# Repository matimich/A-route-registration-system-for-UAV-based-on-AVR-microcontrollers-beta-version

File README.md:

Author: Mateusz Michalski

Description:
A route registration system for UAV, based on AVR microcontrollers is a platform consisting of three ATmega microcontrollers, GPS module and an MicroSD card drive. One of the aims of the project was to learn as much communication interfaces as possible, that is why the project includes UART, I2C, SPI, CAN interfaces. All code has been written in C language. To communicate with MicroSD card drive "FatFs" library has been used. In addition, to make communication with CAN, MCP2515 module and MCP2551 transciver have been used. Working with this components reqiured to attached additional elements from "" library into the project.
Because project was made mostly for a educational purposes, apart from 

The project was made as diploma thesis.

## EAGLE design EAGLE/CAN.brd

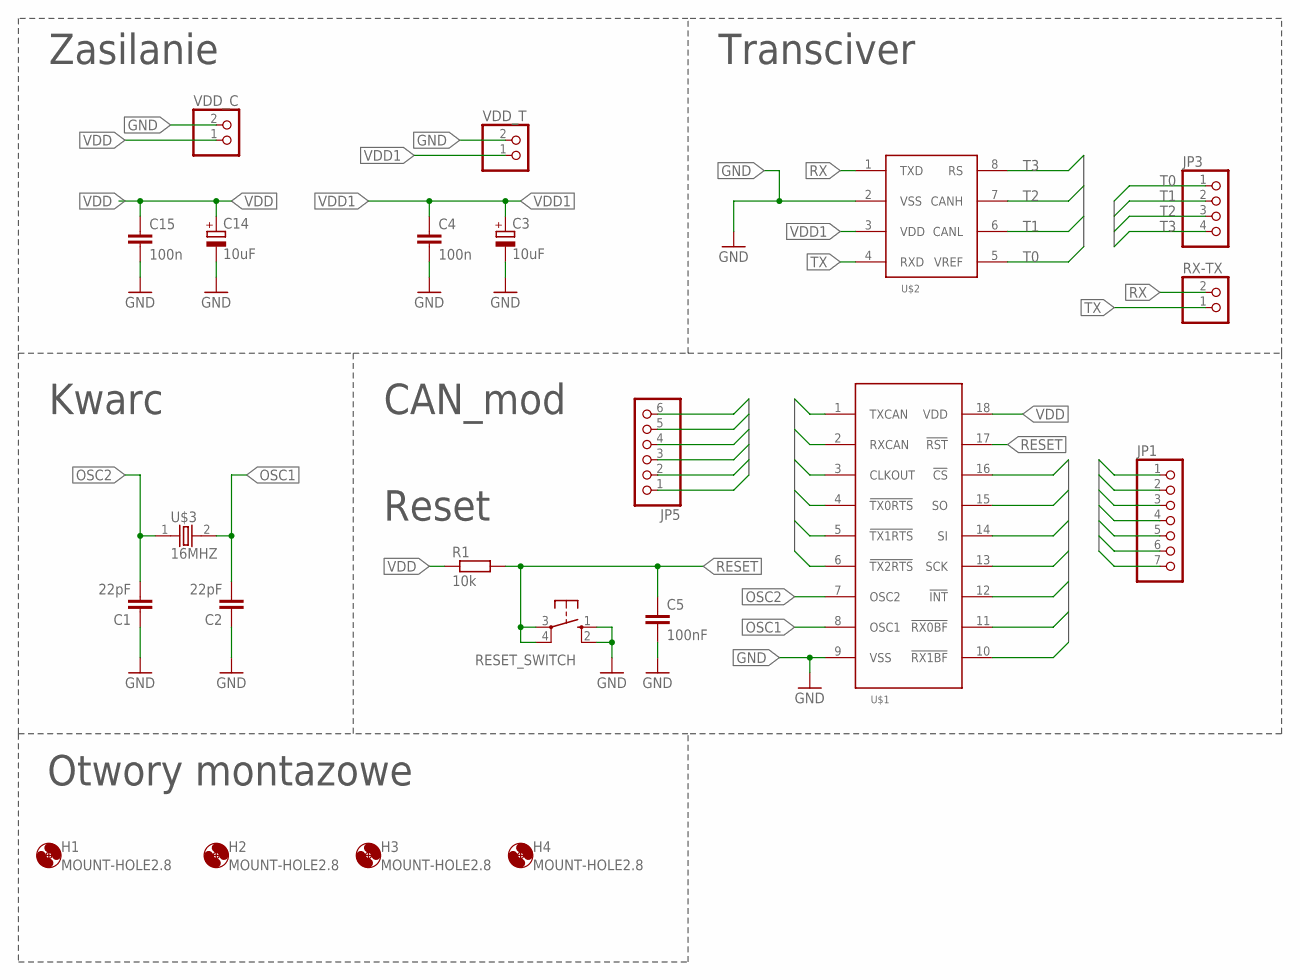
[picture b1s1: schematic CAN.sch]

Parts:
C1, C2: 22pF; C3216
C3, C14: 10uF; A/3216-18W
C4, C15: 100n; C1206K
C5: 100nF; C1206K
H1, H2, H3, H4: MOUNT-HOLE2.8; 2,8
JP1: PINHD-1X7MAT_LCD; 1X07
JP3: PINHD-1X4; 1X04
JP5: PINHD-1X6MAT6; 1X06
R1: 10k; R3216
RESET_SWITCH: 10-XX; B3F-10XX
RX-TX: PINHD-1X2; 1X02
U$1: MCP2515
U$2: MCP2551
U$3: 16MHZ; HC49SM
VDD_C: PINHD-1X2; 1X02
VDD_T: PINHD-1X2; 1X02

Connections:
CAN0: JP1.1, U$1.10 (!RX1BF)
CAN1: JP1.2, U$1.11 (!RX0BF)
CAN2: JP1.3, U$1.12 (!INT)
CAN3: JP1.4, U$1.13 (SCK)
CAN4: JP1.5, U$1.14 (SI)
CAN5: JP1.6, U$1.15 (SO)
CAN6: JP1.7, U$1.16 (!CS)
CANL0: JP5.1, U$1.6 (!TX2RTS)
CANL1: JP5.2, U$1.5 (!TX1RTS)
CANL2: JP5.3, U$1.4 (!TX0RTS)
CANL3: JP5.4, U$1.3 (CLKOUT)
CANL4: JP5.5, U$1.2 (RXCAN)
CANL5: JP5.6, U$1.1 (TXCAN)
GND: C1.1, C2.1, C3.-, C4.2, C5.2, C14.-, C15.2, RESET_SWITCH.1 (S), RESET_SWITCH.2 (S1), U$1.9 (VSS), U$2.2 (VSS), VDD_C.2 (1), VDD_T.2 (1)
OSC1: C2.2, U$1.8 (OSC1), U$3.2
OSC2: C1.2, U$1.7 (OSC2), U$3.1
RESET: C5.1, R1.2, RESET_SWITCH.3, RESET_SWITCH.4 (P1), U$1.17 (!RST)
RX: RX-TX.2 (1), U$2.1 (TXD)
T0: JP3.1, U$2.5 (VREF)
T1: JP3.2, U$2.6 (CANL)
T2: JP3.3, U$2.7 (CANH)
T3: JP3.4, U$2.8 (RS)
TX: RX-TX.1 (2), U$2.4 (RXD)
VDD: C14.+, C15.1, R1.1, U$1.18 (VDD), VDD_C.1 (2)
VDD1: C3.+, C4.1, U$2.3 (VDD), VDD_T.1 (2)

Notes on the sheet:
Zasilanie
Transciver
Kwarc
CAN_mod
Reset
Otwory montazowe

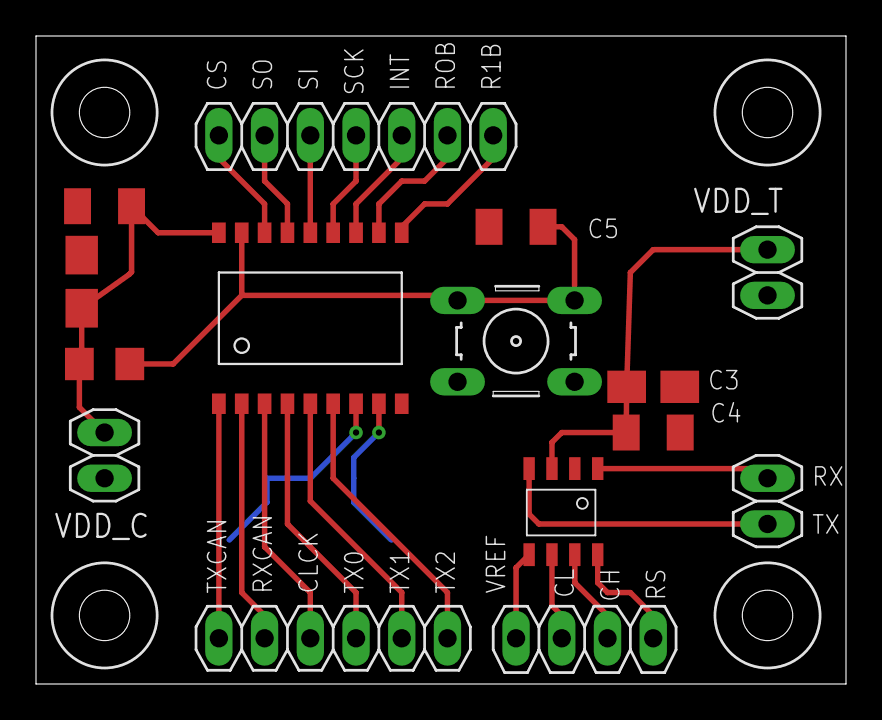
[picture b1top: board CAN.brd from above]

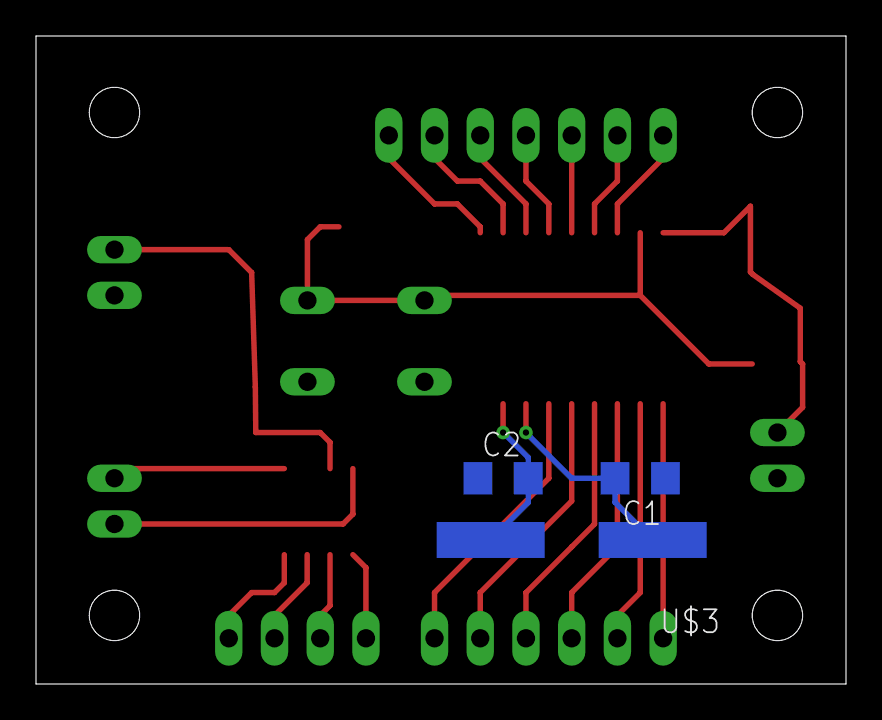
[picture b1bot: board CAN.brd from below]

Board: 2 copper layers, 45.0 x 36.0 mm, 22 parts (3 on the bottom side), 25 nets.

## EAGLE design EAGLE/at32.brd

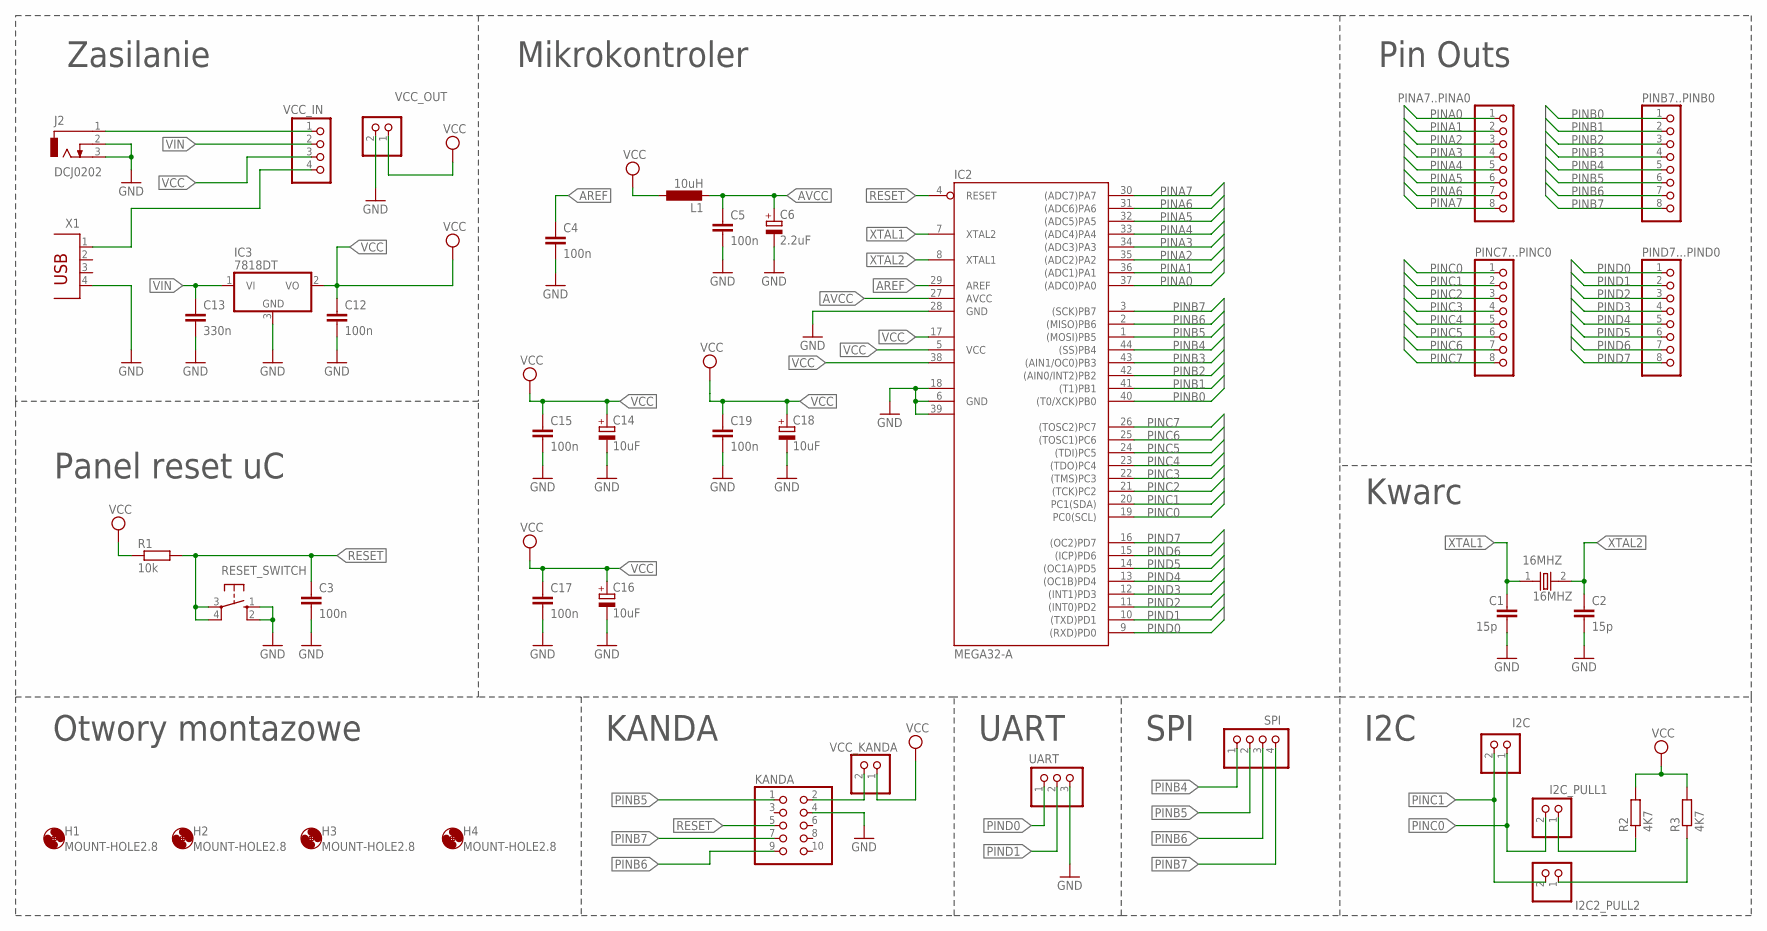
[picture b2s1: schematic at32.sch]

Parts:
16MHZ: 16MHZ; HC49SM
C1, C2: 15p; C1206K
C3, C4, C5, C12, C15, C17, C19: 100n; C1206K
C6: 2.2uF; A/3216-18W
C13: 330n; C1206K
C14, C16, C18: 10uF; A/3216-18W
H1, H2, H3, H4: MOUNT-HOLE2.8; 2,8
I2C, I2C2_PULL2, I2C_PULL1: PINHD-1X2; 1X02
IC2: MEGA32-A; TQFP44
IC3: 7818DT; TO252
J2: DCJ0202
KANDA: PINHD-2X5; 2X05
L1: 10uH; L3225M
PINA7..PINA0: PINHD-1X8MAT8; 1X08
PINB7..PINB0: PINHD-1X8MAT8; 1X08
PINC7...PINC0: PINHD-1X8MAT8; 1X08
PIND7...PIND0: PINHD-1X8MAT8; 1X08
R1: 10k; R3216
R2, R3: 4K7; R3216
RESET_SWITCH: 10-XX; B3F-10XX
SPI: PINHD-1X4; 1X04
UART: PINHD-1X3; 1X03
VCC_IN: PINHD-1X4; 1X04
VCC_KANDA: PINHD-1X2; 1X02
VCC_OUT: PINHD-1X2; 1X02
X1: PN87520

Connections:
AREF: C4.1, IC2.29 (AREF)
AVCC: C5.1, C6.+, IC2.27 (AVCC), L1.2
GND: C1.2, C2.2, C3.2, C4.2, C5.2, C6.-, C12.2, C13.2, C14.-, C15.2, C16.-, C17.2, C18.-, C19.2, IC2.6 (GND), IC2.18 (GND1), IC2.28 (GND), IC2.39 (GND2), IC3.3 (GND), J2.2, J2.3, KANDA.4, RESET_SWITCH.1 (S), RESET_SWITCH.2 (S1), UART.3, VCC_OUT.2 (1), X1.4
unnamed: I2C2_PULL2.1 (2), R3.1
unnamed: J2.1, VCC_IN.1
unnamed: I2C_PULL1.1 (2), R2.1
unnamed: VCC_IN.4, X1.1
unnamed: KANDA.2, VCC_KANDA.2 (1)
PINA0: IC2.37 ((ADC0)PA0), PINA7..PINA0.1
PINA1: IC2.36 ((ADC1)PA1), PINA7..PINA0.2
PINA2: IC2.35 ((ADC2)PA2), PINA7..PINA0.3
PINA3: IC2.34 ((ADC3)PA3), PINA7..PINA0.4
PINA4: IC2.33 ((ADC4)PA4), PINA7..PINA0.5
PINA5: IC2.32 ((ADC5)PA5), PINA7..PINA0.6
PINA6: IC2.31 ((ADC6)PA6), PINA7..PINA0.7
PINA7: IC2.30 ((ADC7)PA7), PINA7..PINA0.8
PINB0: IC2.40 ((T0/XCK)PB0), PINB7..PINB0.1
PINB1: IC2.41 ((T1)PB1), PINB7..PINB0.2
PINB2: IC2.42 ((AIN0/INT2)PB2), PINB7..PINB0.3
PINB3: IC2.43 ((AIN1/OC0)PB3), PINB7..PINB0.4
PINB4: IC2.44 ((SS)PB4), PINB7..PINB0.5, SPI.1
PINB5: IC2.1 ((MOSI)PB5), KANDA.1, PINB7..PINB0.6, SPI.2
PINB6: IC2.2 ((MISO)PB6), KANDA.9, PINB7..PINB0.7, SPI.3
PINB7: IC2.3 ((SCK)PB7), KANDA.7, PINB7..PINB0.8, SPI.4
PINC0: I2C.1 (2), I2C_PULL1.2 (1), IC2.19 (PC0(SCL)), PINC7...PINC0.1
PINC1: I2C.2 (1), I2C2_PULL2.2 (1), IC2.20 (PC1(SDA)), PINC7...PINC0.2
PINC2: IC2.21 ((TCK)PC2), PINC7...PINC0.3
PINC3: IC2.22 ((TMS)PC3), PINC7...PINC0.4
PINC4: IC2.23 ((TDO)PC4), PINC7...PINC0.5
PINC5: IC2.24 ((TDI)PC5), PINC7...PINC0.6
PINC6: IC2.25 ((TOSC1)PC6), PINC7...PINC0.7
PINC7: IC2.26 ((TOSC2)PC7), PINC7...PINC0.8
PIND0: IC2.9 ((RXD)PD0), PIND7...PIND0.1, UART.1
PIND1: IC2.10 ((TXD)PD1), PIND7...PIND0.2, UART.2
PIND2: IC2.11 ((INT0)PD2), PIND7...PIND0.3
PIND3: IC2.12 ((INT1)PD3), PIND7...PIND0.4
PIND4: IC2.13 ((OC1B)PD4), PIND7...PIND0.5
PIND5: IC2.14 ((OC1A)PD5), PIND7...PIND0.6
PIND6: IC2.15 ((ICP)PD6), PIND7...PIND0.7
PIND7: IC2.16 ((OC2)PD7), PIND7...PIND0.8
RESET: C3.1, IC2.4 (RESET), KANDA.5, R1.2, RESET_SWITCH.3, RESET_SWITCH.4 (P1)
VCC: C12.1, C14.+, C15.1, C16.+, C17.1, C18.+, C19.1, IC2.5 (VCC), IC2.17 (VCC1), IC2.38 (VCC2), IC3.2 (VO), L1.1, R1.1, R2.2, R3.2, VCC_IN.3, VCC_KANDA.1 (2), VCC_OUT.1 (2)
VIN: C13.1, IC3.1 (VI), VCC_IN.2
XTAL1: 16MHZ.1, C1.1, IC2.7 (XTAL2)
XTAL2: 16MHZ.2, C2.1, IC2.8 (XTAL1)

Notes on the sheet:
Panel reset uC
Otwory montazowe
Zasilanie
Mikrokontroler
Pin Outs
Kwarc
KANDA
UART
SPI
I2C

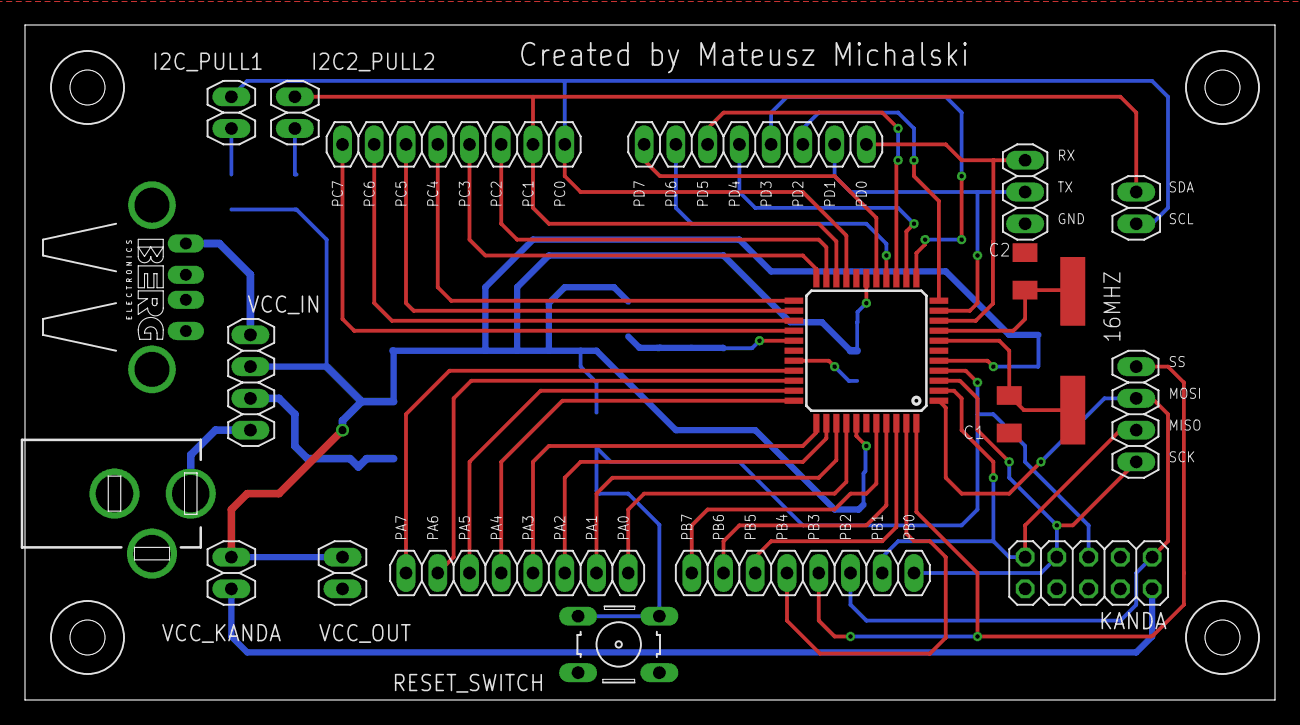
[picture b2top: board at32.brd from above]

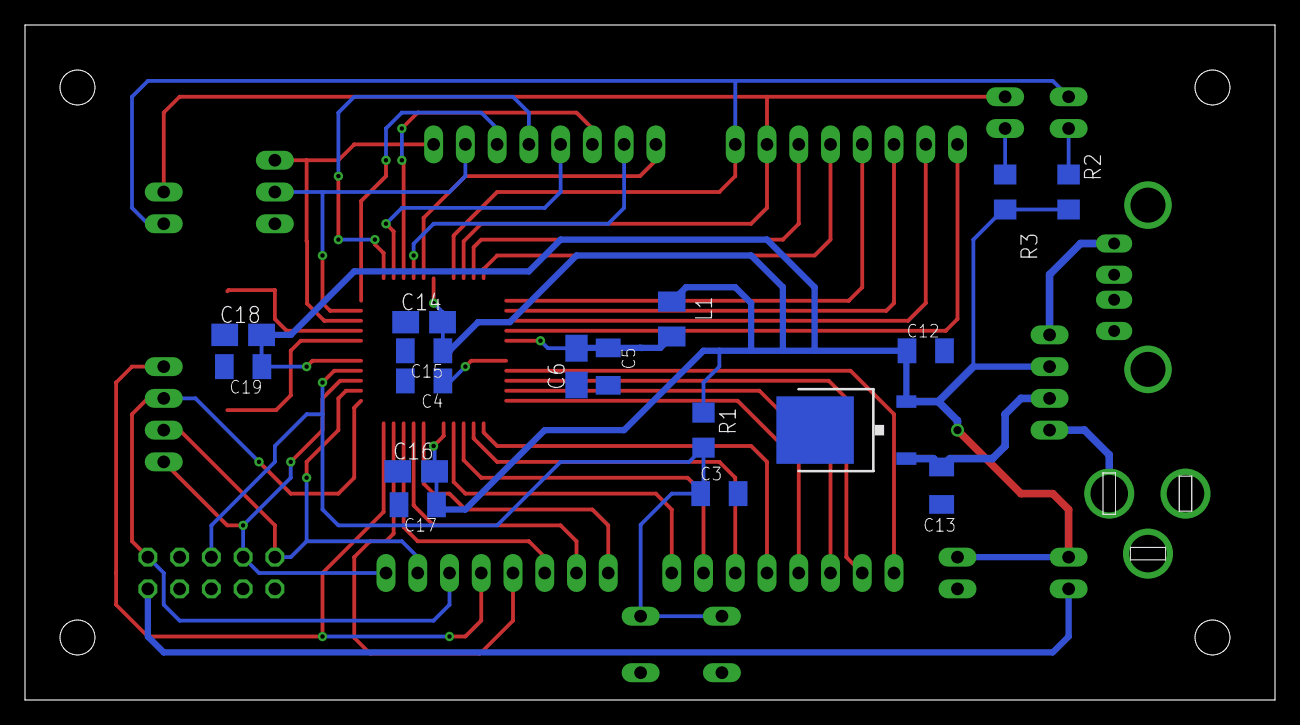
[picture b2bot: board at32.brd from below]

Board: 2 copper layers, 100.0 x 54.0 mm, 41 parts (17 on the bottom side), 45 nets.

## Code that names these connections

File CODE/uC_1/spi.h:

/*
 *  spi.h
 *
 *  Author	: Mateusz Michalski
 *  uC	 	: Atmel AVR ATmega 32
 *  Compiler 	: avr-gcc
 */

#ifndef SPI_H_
#define SPI_H_

//FOR ATMEGA 32
#define MOSI PB5
#define MISO PB6
#define SCK	PB7
#define CS PB4
#define CS_2 PB3

void InitSPI(void);	// SPI INITIALIZATION
void SPI_sent(uint8_t data);	//SENDING SIGN
uint8_t SPI_receive(void);	//RECEIVING SIGN
uint8_t SPI_T_R(uint8_t data);	// SEND/RECEIVE SIGN SIMULTANEOUSLY

#endif /* SPI_H_ */

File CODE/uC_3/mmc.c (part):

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#define CT_BLOCK	0x08		/* Block addressing */

/* Port Controls  (Platform dependent) */
#define CS_LOW()	PORTB &= ~(1<<PB4)		/* MMC CS = L */
#define	CS_HIGH()	PORTB |= (1<<PB4)		/* MMC CS = H */

#define SOCKPORT	PINC			/* Socket contact port */
#define SOCKWP		(1<<PC3)			/* Write protect switch (PB5) */
#define SOCKINS		(1<<PC2)			/* Card detect switch (PB4) */

#define	FCLK_SLOW()	(SPCR |= (1<<SPR1)) 		/* Set slow clock (100k-400k) */
#define	FCLK_FAST()	(SPCR &= (~((1<<SPR0)|(1<<SPR1) )))		/* Set fast clock (depends on the CSD) */
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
